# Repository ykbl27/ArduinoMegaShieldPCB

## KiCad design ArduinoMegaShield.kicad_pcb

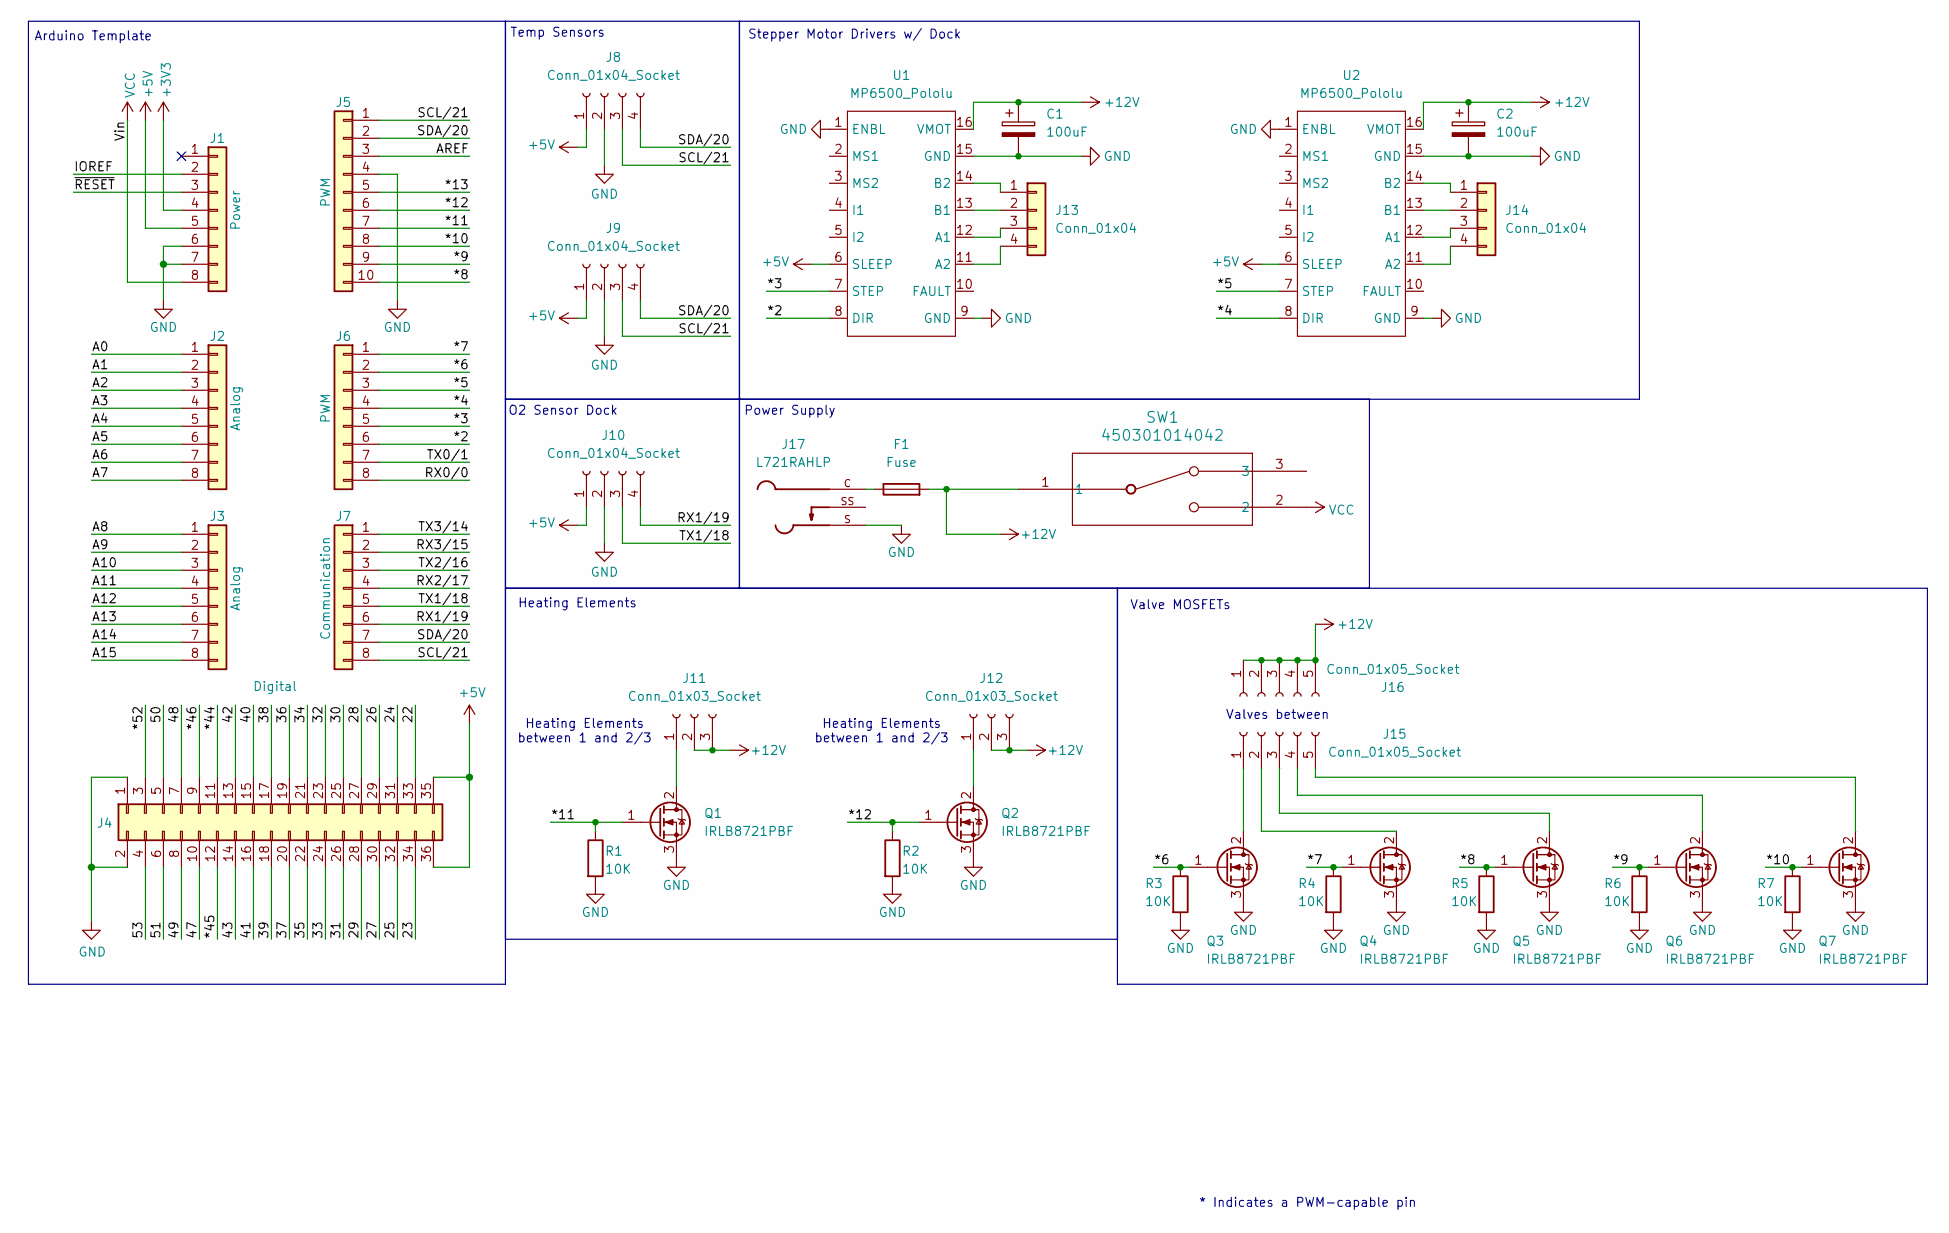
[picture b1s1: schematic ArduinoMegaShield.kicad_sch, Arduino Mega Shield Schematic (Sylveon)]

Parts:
C1, C2: 100uF; CP_Radial_D6.3mm_P2.50mm
F1: Fuse; Fuseholder_TR5_Littelfuse_No560_No460
J1: Power; PinSocket_1x08_P2.54mm_Vertical
J2, J3: Analog; PinSocket_1x08_P2.54mm_Vertical
J4: Digital; PinSocket_2x18_P2.54mm_Vertical
J5: PWM; PinSocket_1x10_P2.54mm_Vertical
J6: PWM; PinSocket_1x08_P2.54mm_Vertical
J7: Communication; PinSocket_1x08_P2.54mm_Vertical
J8, J9, J10: Conn_01x04_Socket; PinSocket_1x04_P2.54mm_Vertical
J11, J12: Conn_01x03_Socket; PinSocket_1x03_P2.54mm_Vertical
J13, J14: Conn_01x04; JST_XH_B4B-XH-A_1x04_P2.50mm_Vertical
J15, J16: Conn_01x05_Socket; PinSocket_1x05_P2.54mm_Vertical
J17: L721RAHLP; SWITCHCRAFT_L721RAHLP; PARTREV A
Q1, Q2, Q3, Q4, Q5, Q6, Q7: IRLB8721PBF; TO-220-3_Vertical
R1, R2, R3, R4, R5, R6, R7: 10K; R_0805_2012Metric_Pad1.20x1.40mm_HandSolder
SW1: 450301014042; SW_450301014042_WRE
U1, U2: MP6500_Pololu; Pololu_Breakout-16_15.2x20.3mm

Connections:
+3V3: J1.4
+5V: J1.5, J4.35, J4.36, J8.1, J9.1, J10.1, U1.6 (SLEEP), U2.6 (SLEEP)
+12V: C1.1, C2.1, F1.2, J11.2, J11.3, J12.2, J12.3, J16.1, J16.2, J16.3, J16.4, J16.5, SW1.1, U1.16 (VMOT), U2.16 (VMOT)
/22: J4.33
/23: J4.34
/24: J4.31
/25: J4.32
/26: J4.29
/27: J4.30
/28: J4.27
/29: J4.28
/30: J4.25
/31: J4.26
/32: J4.23
/33: J4.24
/34: J4.21
/35: J4.22
/36: J4.19
/37: J4.20
/38: J4.17
/39: J4.18
/40: J4.15
/41: J4.16
/42: J4.13
/43: J4.14
/47: J4.10
/48: J4.7
/49: J4.8
/50: J4.5
/51: J4.6
/53: J4.4
/*2: J6.6, U1.8 (DIR)
/*3: J6.5, U1.7 (STEP)
/*4: J6.4, U2.8 (DIR)
/*5: J6.3, U2.7 (STEP)
/*6: J6.2, Q3.1 (G), R3.1
/*7: J6.1, Q4.1 (G), R4.1
/*8: J5.10, Q5.1 (G), R5.1
/*9: J5.9, Q6.1 (G), R6.1
/*10: J5.8, Q7.1 (G), R7.1
/*11: J5.7, Q1.1 (G), R1.1
/*12: J5.6, Q2.1 (G), R2.1
/*13: J5.5
/*44: J4.11
/*45: J4.12
/*46: J4.9
/*52: J4.3
/A0: J2.1
/A1: J2.2
/A2: J2.3
/A3: J2.4
/A4: J2.5
/A5: J2.6
/A6: J2.7
/A7: J2.8
/A8: J3.1
/A9: J3.2
/A10: J3.3
/A11: J3.4
/A12: J3.5
/A13: J3.6
/A14: J3.7
/A15: J3.8
/AREF: J5.3
/IOREF: J1.2
/RX0/0: J6.8
/RX1/19: J7.6, J10.4
/RX2/17: J7.4
/RX3/15: J7.2
/SCL/21: J5.1, J7.8, J8.3, J9.3
/SDA/20: J5.2, J7.7, J8.4, J9.4
/TX0/1: J6.7
/TX1/18: J7.5, J10.3
/TX2/16: J7.3
/TX3/14: J7.1
/~RESET: J1.3
GND: C1.2, C2.2, J1.6, J1.7, J4.1, J4.2, J5.4, J8.2, J9.2, J10.2, J17.S, Q1.3 (S), Q2.3 (S), Q3.3 (S), Q4.3 (S), Q5.3 (S), Q6.3 (S), Q7.3 (S), R1.2, R2.2, R3.2, R4.2, R5.2, R6.2, R7.2, U1.1 (ENBL), U1.9 (GND), U1.15 (GND), U2.1 (ENBL), U2.9 (GND), U2.15 (GND)
unnamed: F1.1, J17.C
unnamed: J11.1, Q1.2 (D)
unnamed: J12.1, Q2.2 (D)
unnamed: J13.1, U1.14 (B2)
unnamed: J13.2, U1.13 (B1)
unnamed: J13.3, U1.12 (A1)
unnamed: J13.4, U1.11 (A2)
unnamed: J14.1, U2.14 (B2)
unnamed: J14.2, U2.13 (B1)
unnamed: J14.3, U2.12 (A1)
unnamed: J14.4, U2.11 (A2)
unnamed: J15.1, Q3.2 (D)
unnamed: J15.2, Q4.2 (D)
unnamed: J15.3, Q5.2 (D)
unnamed: J15.4, Q6.2 (D)
unnamed: J15.5, Q7.2 (D)
VCC: J1.8, SW1.2

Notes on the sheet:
Stepper Motor Drivers w/ Dock
Valve MOSFETs
Heating Elements between 1 and 2/3
Power Supply
Temp Sensors
Heating Elements
Valves between
Arduino Template
* Indicates a PWM-capable pin
O2 Sensor Dock

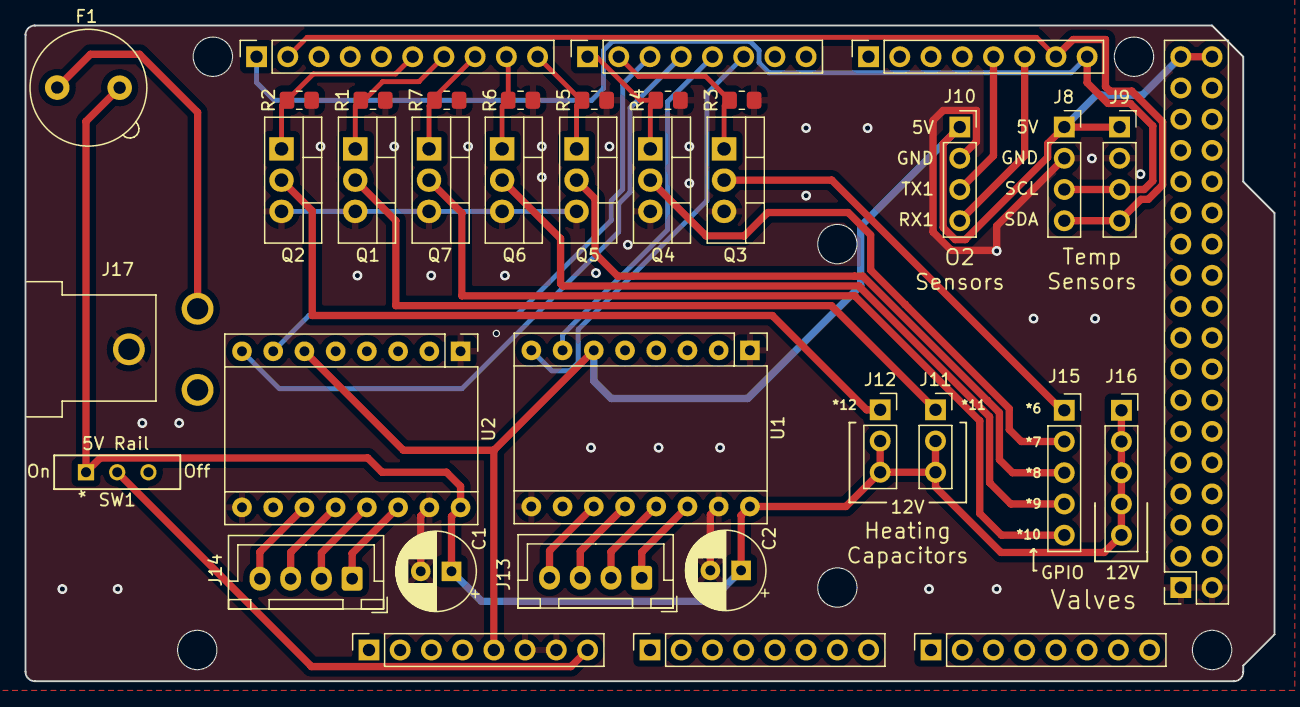
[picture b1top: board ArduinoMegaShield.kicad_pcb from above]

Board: 2 copper layers, 101.6 x 53.3 mm, 43 parts (0 on the bottom side), 35 nets.

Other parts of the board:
MH1, MH2, MH3, MH4, MH5, MH6: MountingHole_3.2mm

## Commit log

2024-05-23 draft schematic
2024-06-01 Finished Schematic
2024-06-06 Layout Placement done
    -no fuse yet
2024-06-13 Final Layout
2024-06-24 fixed for DRC
